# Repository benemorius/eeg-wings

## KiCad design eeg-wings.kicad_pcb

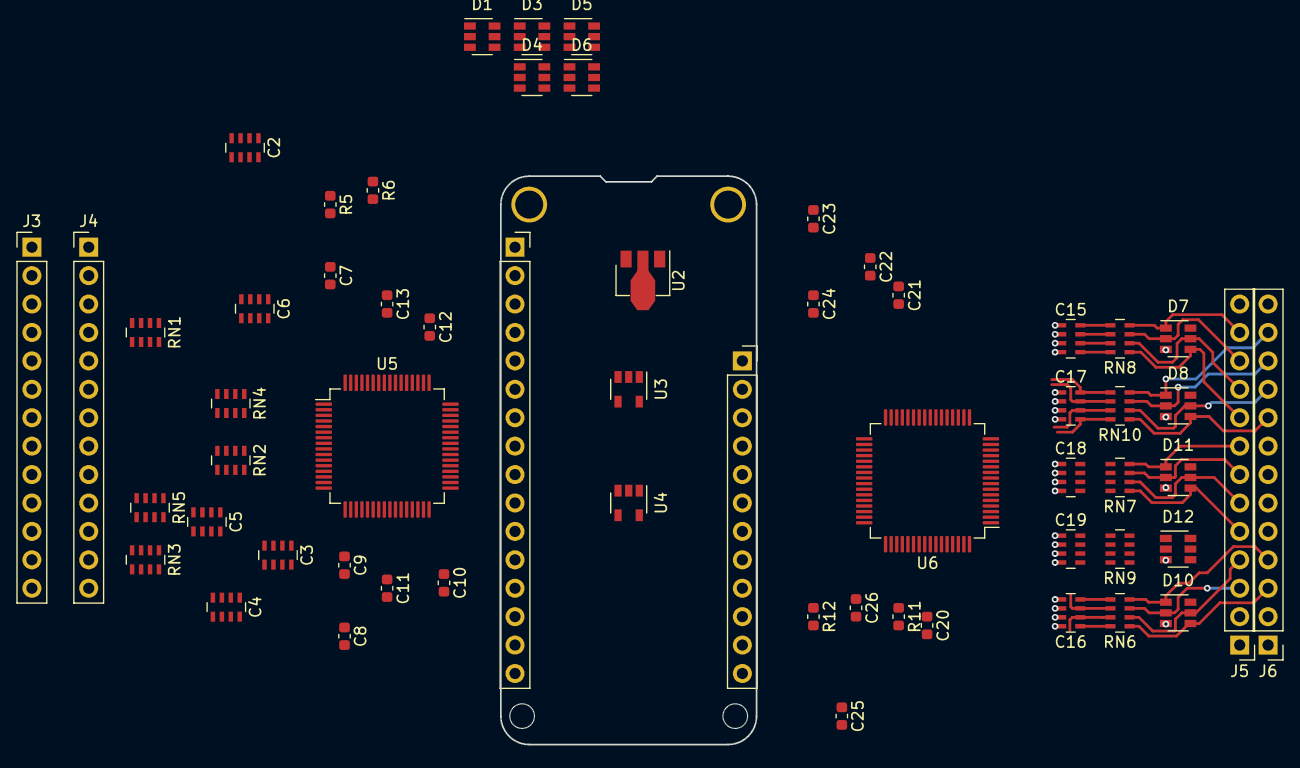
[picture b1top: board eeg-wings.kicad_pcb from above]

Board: 4 copper layers, 22.9 x 50.8 mm, 59 parts (0 on the bottom side), 115 nets.

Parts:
C2, C3, C4, C5, C6, C15, C16, C17, C18, C19: 1nF; R_Array_Concave_4x0603
C7, C20: 1nF; C_0603_1608Metric
C8, C21: 10uF; C_0603_1608Metric
C9, C10, C13, C22, C23, C26: 1uF; C_0603_1608Metric
C11, C24: 100uF; C_0603_1608Metric
C12, C25: 0.1uF; C_0603_1608Metric
D1, D3, D4, D5, D6, D7, D8, D10, D11, D12: D_TVS_4; SOT-23-6
J1: Adafruit Wing Header Left; PinSocket_1x16_P2.54mm_Vertical
J2: Adafruit Wing Header Right; PinSocket_1x12_P2.54mm_Vertical
J3, J4, J5, J6: Conn_01x13; PinHeader_1x13_P2.54mm_Vertical
R5, R11: 1M; R_0603_1608Metric
R6, R12: 10k; R_0603_1608Metric
RN1, RN2, RN3, RN4, RN5, RN6, RN7, RN8, RN9, RN10: 2k2; R_Array_Concave_4x0603
U2: MCP1754-3302E_SOT89; SOT-89-3
U3: TLV70025_SOT23-5; SOT-23-5
U4: TPS72325_SOT23-5; SOT-23-5
U5, U6: ADS1299; TQFP-64_10x10mm_P0.5mm

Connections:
/-3.3V: U4.2, U4.3
/A0: J1.5, U5.38
/A1: J1.6, U5.46
/A2: J1.7, U5.45
/A3: J1.8, U5.44
/A4: J1.9, U5.42
/A5: J1.10, U5.47
/Analog-Left/1N: D1.2, J3.11, RN5.3
/Analog-Left/1P: D3.2, J4.11, RN3.3
/Analog-Left/2N: D1.5, J3.10, RN5.2
/Analog-Left/2P: D3.5, J4.10, RN3.2
/Analog-Left/3N: D1.4, J3.9, RN5.1
/Analog-Left/3P: D3.4, J4.9, RN3.1
/Analog-Left/4N: D6.1, J3.8, RN4.4
/Analog-Left/4P: D4.1, J4.8, RN2.4
/Analog-Left/5N: D6.2, J3.7, RN4.3
/Analog-Left/5P: D4.2, J4.7, RN2.3
/Analog-Left/6N: D6.5, J3.6, RN4.2
/Analog-Left/6P: D4.5, J4.6, RN2.2
/Analog-Left/7N: D6.4, J3.5, RN4.1
/Analog-Left/7P: D4.4, J4.5, RN2.1
/Analog-Left/8N: D5.1, J3.4, RN1.4
/Analog-Left/8P: D5.5, J4.4, RN1.2
/Analog-Left/8PA: C2.2, RN1.7, U5.2
/Analog-Left/BIAS: D5.2, D5.4, J3.3, J4.3, RN1.1, RN1.3
/Analog-Left/BIAS_DRV: C2.1, C2.3, C7.2, R5.1, RN1.6, RN1.8
/Analog-Left/SRB1: D3.1, J4.12, RN3.4
/Analog-Left/SRB2: D1.1, J3.12, RN5.4
/Analog-Right/1N: D8.2, J6.11, RN10.3
/Analog-Right/1P: D7.2, J5.11, RN8.3
/Analog-Right/2N: D8.5, J6.10, RN10.2
/Analog-Right/2P: D7.5, J5.10, RN8.2
/Analog-Right/3N: D8.4, J6.9, RN10.1
/Analog-Right/3P: D7.4, J5.9, RN8.1
/Analog-Right/4N: D12.1, J6.8, RN9.4
/Analog-Right/4P: D11.1, J5.8, RN7.4
/Analog-Right/5N: D12.2, J6.7, RN9.3
/Analog-Right/5P: D11.2, J5.7, RN7.3
/Analog-Right/6N: D12.5, J6.6, RN9.2
/Analog-Right/6P: D11.5, J5.6, RN7.2
/Analog-Right/7N: D12.4, J6.5, RN9.1
/Analog-Right/7P: D11.4, J5.5, RN7.1
/Analog-Right/8N: D10.1, J6.4, RN6.4
/Analog-Right/8P: D10.5, J5.4, RN6.2
/Analog-Right/8PA: C16.2, RN6.7, U6.2
/Analog-Right/BIAS: D10.2, D10.4, J5.3, J6.3, RN6.1, RN6.3
/Analog-Right/BIAS_DRV: C16.1, C16.3, C20.2, R11.1, RN6.6, RN6.8
/Analog-Right/SRB1: D7.1, J5.12, RN8.4
/Analog-Right/SRB2: D8.1, J6.12, RN10.4
/D1: J2.4, U6.38
/D2: J2.5, U6.46
/D3: J2.6, U6.45
/D4: J2.7, U6.44
/D5: J2.8, U6.42
/D6: J2.9, U6.47
/MISO: J1.13, U5.43, U6.43
/MOSI: J1.12, U5.34, U6.34
/PWDN: J2.10, U5.35, U6.35
/RESET: J1.1, U5.36, U6.36
/SCLK: J1.11, U5.40, U6.40
/SDA: J2.12, U5.39
/SDL: J2.11, U6.39
/VBAT: J2.1, U2.1
GND: C2.5, C2.6, C2.7, C2.8, C3.1, C3.2, C3.3, C3.4, C4.1, C4.2, C4.3, C4.4, C5.1, C5.2, C5.3, C5.4, C6.1, C6.2, C6.3, C6.4, C15.1, C15.2, C15.3, C15.4, C16.5, C16.6, C16.7, C16.8, C17.1, C17.2, C17.3, C17.4, C18.1, C18.2, C18.3, C18.4, C19.1, C19.2, C19.3, C19.4, D1.3, D3.3, D4.3, D5.3, D6.3, D7.3, D8.3, D10.3, D11.3, D12.3, J1.4, J3.2, J4.2, J5.2, J6.2, U2.2, U3.2, U4.1, U5.31, U5.33, U5.49, U5.51, U5.60, U6.31, U6.33, U6.49, U6.51, U6.60
unnamed: C2.4, RN1.5, U5.1
unnamed: C3.5, RN2.8, U5.3
unnamed: C3.6, RN2.7, U5.6
unnamed: C3.7, RN2.6, U5.8
unnamed: C3.8, RN2.5, U5.10
unnamed: C4.5, RN3.8, U5.12
unnamed: C4.6, RN3.7, U5.14
unnamed: C4.7, RN3.6, U5.16
unnamed: C4.8, RN3.5, U5.17
unnamed: C5.5, RN5.8, U5.11
unnamed: C5.6, RN5.7, U5.13
unnamed: C5.7, RN5.6, U5.15
unnamed: C5.8, RN5.5, U5.18
unnamed: C6.5, RN4.8, U5.4
unnamed: C6.6, RN4.7, U5.5
unnamed: C6.7, RN4.6, U5.7
unnamed: C6.8, RN4.5, U5.9
unnamed: C7.1, R5.2, U5.62, U5.63
unnamed: C8.1, U5.24
unnamed: C9.2, U5.26
unnamed: C10.2, U5.30
unnamed: C11.2, U5.28
unnamed: C12.2, C13.2, U5.55
unnamed: C15.5, RN8.8, U6.12
unnamed: C15.6, RN8.7, U6.14
unnamed: C15.7, RN8.6, U6.16
unnamed: C15.8, RN8.5, U6.17
unnamed: C16.4, RN6.5, U6.1
unnamed: C17.5, RN10.8, U6.11
unnamed: C17.6, RN10.7, U6.13
unnamed: C17.7, RN10.6, U6.15
unnamed: C17.8, RN10.5, U6.18
unnamed: C18.5, RN7.8, U6.3
unnamed: C18.6, RN7.7, U6.6
unnamed: C18.7, RN7.6, U6.8
unnamed: C18.8, RN7.5, U6.10
unnamed: C19.5, RN9.8, U6.4
unnamed: C19.6, RN9.7, U6.5
unnamed: C19.7, RN9.6, U6.7
unnamed: C19.8, RN9.5, U6.9
unnamed: C20.1, R11.2, U6.62, U6.63
unnamed: C21.1, U6.24
unnamed: C22.2, U6.26
unnamed: C23.2, U6.30
unnamed: C24.2, U6.28
unnamed: C25.2, C26.2, U6.55
unnamed: R6.1, U5.52
unnamed: R12.1, U6.52
VDD: J1.2, R6.2, R12.2, U2.3, U3.1, U5.48, U5.50, U6.48, U6.50
VDDA: J3.1, J4.1, J5.1, J6.1, U3.5, U5.19, U5.21, U5.22, U5.54, U5.56, U5.59, U6.19, U6.21, U6.22, U6.54, U6.56, U6.59
VSSA: C8.2, C9.1, C10.1, C11.1, C12.1, C13.1, C21.2, C22.1, C23.1, C24.1, C25.1, C26.1, J3.13, J4.13, J5.13, J6.13, U4.5, U5.20, U5.23, U5.25, U5.32, U5.53, U5.57, U5.58, U6.20, U6.23, U6.25, U6.32, U6.53, U6.57, U6.58

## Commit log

2020-09-06 schematic almost done
2020-09-06 almost done with schematic
2020-09-06 schematic
2020-09-17 dunno
